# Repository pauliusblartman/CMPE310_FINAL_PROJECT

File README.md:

# CMPE310_FINAL_PROJECT
Final project for CMPE310.

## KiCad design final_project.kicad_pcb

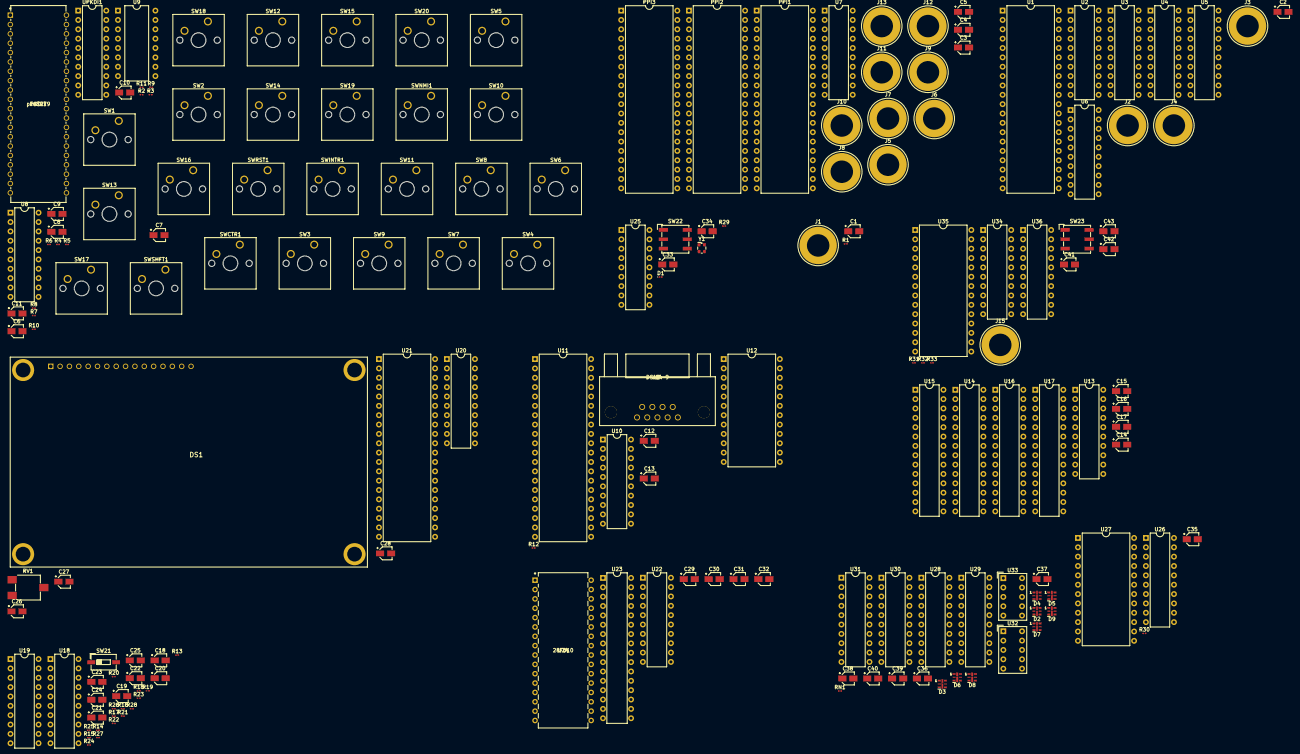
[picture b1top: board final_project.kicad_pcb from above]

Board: 2 copper layers, 173 parts (0 on the bottom side), 213 nets, no tracks yet.

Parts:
C1: 100uF; CP_Elec_3x5.3
C2, C3, C4, C5, C9, C12, C13, C14, C15, C16, C17, C26, C27, C34, C36, C37, C38, C39, C40, C41, C42, C43: 0.1uF; CP_Elec_3x5.3
C6, C7, C8, C10, C11: C; CP_Elec_3x5.3
C18, C19, C20, C21, C22, C23, C24, C25: C_Small; CP_Elec_3x5.3
C28, C29, C30, C31, C32, C35: .0000001; CP_Elec_3x5.3
C33: 10uF; CP_Elec_3x5.3
D1: DIODE; D_0201_0603Metric
D2, D3, D4, D5, D6, D7, D8, D9: LED; LED-APA102-2020
DS1: LCD4x20
J1: Conn_01x02_Female; Banana_Jack_1Pin
J2: Conn_01x20; Banana_Jack_1Pin
J3: Conn_01x16; Banana_Jack_1Pin
J4: Conn_01x10; Banana_Jack_1Pin
J5, J6, J7, J8, J9, J10, J11, J12, J13: Conn_01x08; Banana_Jack_1Pin
J14: DSUB-9
J15: Interrupt Header; Banana_Jack_1Pin
PKDI1: pkd8279
PPI1, PPI2, PPI3: 8255; DIP-40_W15.24mm
R1, R2, R3, R4, R5, R6, R7, R8, R9, R10, R11, R12, R13, R14, R15, R16, R17, R18, R19, R20, R21, R22, R23, R24, R25, R26, R27, R28, R32: R; R_0201_0603Metric
R29, R33: 10k; R_0201_0603Metric
R30, R31: 10000; R_0201_0603Metric
RN1: R_Network08; R_0201_0603Metric
RV1: 10000-20000; Potentiometer_ACP_CA6-VSMD_Vertical
SW1, SW2, SW3, SW4, SW5, SW6, SW7, SW8, SW9, SW10, SW11, SW12, SW13, SW14, SW15, SW16, SW17, SW18, SW19, SW20: SW_Push; SW_Cherry_MX_1.00u_PCB
SW21: SW_DIP_x08; SW_DIP_SPSTx01_Slide_6.7x4.1mm_W6.73mm_P2.54mm_LowProfile_J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
SW22, SW23: SW_Push; Nidec_Copal_SH-7010A
SWCTR1: SW_Push; SW_Cherry_MX_1.00u_PCB
SWINTR1: SW_Push; SW_Cherry_MX_1.00u_PCB
SWNMI1: SW_Push; SW_Cherry_MX_1.00u_PCB
SWRST1: SW_Push; SW_Cherry_MX_1.00u_PCB
SWSHFT1: SW_Push; SW_Cherry_MX_1.00u_PCB
U1: 8086_Min_Mode; DIP-40_W15.24mm
U2, U3: 74LS245; DIP-20_W7.62mm
U4, U5, U6: 74LS373; DIP-20_W7.62mm
U7, U10, U13, U19, U20, U22, U26, U28, U34: PAL16L8; DIP-20_W7.62mm
U8: 74LS540; DIP-20_W7.62mm
U9: 74HC237; DIP-16_W10.16mm
U11: 16550; DIP-40_W15.24mm
U12: max235cpg; DIP-24_W15.24mm
U14, U15, U16, U17: CY7C199; DIP-28_W7.62mm
U18, U36: 74LS244; DIP-20_W7.62mm
U21: 82C55A; DIP-40_W15.24mm
U23: 28F010; DIP-32_W7.62mm
U24: 28F010
U25: 8284; DIP-18_W7.62mm
U27: 8254; DIP-24_W15.24mm
U29, U30, U31: 74LS374; DIP-20_W7.62mm
U32, U33: HDSP-A151
U35: 8259; DIP-28_W15.24mm
UPKDI1: PAL16L8; DIP-20_W7.62mm
Y1: 15MHz; Oscillator_SMD_ECS_2520MV-xxx-xx-4Pin_2.5x2.0mm

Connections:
+3V3: R1.2, U9.4, U9.6
+5V: C1.1, C2.1, C3.1, C4.1, C5.1, C9.2, C12.2, C13.1, C14.1, C15.1, C16.1, C17.1, C26.1, C27.1, C28.2, C31.1, C32.1, C34.1, C35.1, C36.1, C37.1, C38.1, C39.1, C40.1, C41.1, C42.1, C43.2, D1.2, DS1.2, J1.1, PKDI1.40, PPI1.26, PPI2.26, PPI3.26, R1.1, R2.1, R4.1, R6.1, R8.1, R10.1, R12.2, R13.2, R14.2, R15.2, R16.2, R17.2, R18.2, R19.2, R20.2, R29.1, R30.1, R31.2, R33.1, RN1.1, RV1.3, SW23.2, U1.33, U1.40, U2.20, U3.20, U4.20, U5.20, U6.20, U7.20, U8.20, U9.16, U10.20, U11.40, U12.12, U13.20, U14.28, U15.28, U16.28, U17.28, U18.20, U19.20, U20.20, U21.26, U22.20, U23.17, U23.18, U23.19, U23.20, U23.21, U23.23, U23.25, U23.26, U23.27, U23.28, U23.29, U23.32, U24.17, U24.18, U24.19, U24.20, U24.21, U24.23, U24.25, U24.26, U24.27, U24.28, U24.29, U24.32, U25.18, U27.24, U28.20, U29.20, U30.20, U31.20, U32.1, U32.6, U33.1, U33.6, U34.20, U35.28, U36.20, UPKDI1.20
+12V: C29.2, C30.2, U23.1, U24.1
/8086/A0: J2.1, U4.2, U7.13, U10.1, U13.1, U19.11, U20.1, U26.1, UPKDI1.1
/8086/A1: PKDI1.21, PPI1.9, PPI2.9, PPI3.9, U4.5, U11.28, U14.21, U15.21, U16.21, U17.21, U19.9, U21.9, U27.19
/8086/A2: PPI1.8, PPI2.8, PPI3.8, U4.6, U11.27, U14.23, U15.23, U16.23, U17.23, U19.8, U21.8, U27.20, UPKDI1.2
/8086/A3: U4.9, U7.12, U11.26, U14.24, U15.24, U16.24, U17.24, U19.7, U20.2, U26.2, UPKDI1.3
/8086/A4: U4.12, U7.1, U10.2, U14.25, U15.25, U16.25, U17.25, U19.6, U20.3, U26.3, UPKDI1.4
/8086/A5: U4.15, U7.2, U10.3, U14.26, U15.26, U16.26, U17.26, U19.5, U20.4, U26.4, UPKDI1.5
/8086/A6: U4.16, U7.3, U10.4, U14.1, U15.1, U16.1, U17.1, U19.4, U20.5, U26.5, UPKDI1.6
/8086/A7: U4.19, U7.4, U10.5, U14.2, U15.2, U16.2, U17.2, U19.3, U20.6, U26.6, UPKDI1.7
/8086/A8: U6.2, U7.5, U10.6, U14.3, U15.3, U16.3, U17.3, U19.2, U20.7, U26.7, UPKDI1.8
/8086/A9: U6.5, U7.6, U10.7, U14.4, U15.4, U16.4, U17.4, U19.1, U20.8, U26.8, UPKDI1.9
/8086/A10: U6.6, U7.7, U10.8, U14.5, U15.5, U16.5, U17.5, U19.14, U20.9, U26.9, UPKDI1.11
/8086/A11: U6.9, U7.8, U10.9, U14.6, U15.6, U16.6, U17.6, U19.15, U20.11, U26.11
/8086/A12: U6.12, U7.9, U10.19, U14.7, U15.7, U16.7, U17.7, U19.16, U20.12, UPKDI1.15
/8086/A13: U6.15, U7.11, U10.18, U14.8, U15.8, U16.8, U17.8, U19.17, U20.13, U26.12, UPKDI1.14
/8086/A14: U6.16, U7.14, U10.17, U14.9, U15.9, U16.9, U17.9, U19.18, U20.14, U26.13, UPKDI1.13
/8086/A15: U6.19, U7.15, U10.16, U14.10, U15.10, U16.10, U17.10, U19.19, U20.15, U26.14, UPKDI1.12
/8086/A16: U5.2, U13.2
/8086/A17: U5.5, U13.3
/8086/A18: U5.6, U13.4
/8086/A19: U5.9, U13.5
/8086/AD0: U1.16, U2.2, U4.3
/8086/AD1: U1.15, U2.3, U4.4
/8086/AD2: U1.14, U2.4, U4.7
/8086/AD3: U1.13, U2.5, U4.8
/8086/AD4: U1.12, U2.6, U4.13
/8086/AD5: U1.11, U2.7, U4.14
/8086/AD6: U1.10, U2.8, U4.17
/8086/AD7: U1.9, U2.9, U4.18
/8086/AD8: U1.8, U3.2, U6.3
/8086/AD9: U1.7, U3.3, U6.4
/8086/AD10: U1.6, U3.4, U6.7
/8086/AD11: U1.5, U3.5, U6.8
/8086/AD12: U1.4, U3.6, U6.13
/8086/AD13: U1.3, U3.7, U6.14
/8086/AD14: U1.2, U3.8, U6.17
/8086/AD15: U1.39, U3.9, U6.18
/8086/BHE': J4.1, U1.34, U13.6, U22.3
/8086/CLK: U1.19, U25.8, U27.9, U27.15, U27.18
/8086/D0: DS1.7, J3.1, PKDI1.12, PPI2.34, U2.18, U15.11, U17.11, U18.18, U21.4, U21.34
/8086/D1: DS1.8, PKDI1.13, PPI2.33, U2.17, U15.12, U17.12, U18.16, U21.3, U21.33
/8086/D2: DS1.9, PKDI1.14, PPI2.32, U2.16, U15.13, U17.13, U18.14, U21.2, U21.32
/8086/D3: DS1.10, PKDI1.15, PPI2.31, U2.15, U15.15, U17.15, U18.12, U21.1, U21.31
/8086/D4: DS1.11, PKDI1.16, PPI2.30, U2.14, U15.16, U17.16, U18.9, U21.30, U21.40
/8086/D5: DS1.12, PKDI1.17, PPI2.29, U2.13, U15.17, U17.17, U18.7, U21.29, U21.39
/8086/D6: DS1.13, PKDI1.18, PPI2.28, U2.12, U15.18, U17.18, U18.5, U21.28, U21.38
/8086/D7: DS1.14, PKDI1.19, PPI2.27, U2.11, U15.19, U17.19, U18.3, U21.27, U21.37
/8086/D8: PPI1.34, PPI3.34, U3.18, U11.1, U14.11, U16.11
/8086/D9: PPI1.33, PPI3.33, U3.17, U11.2, U14.12, U16.12
/8086/D10: PPI1.32, PPI3.32, U3.16, U11.3, U14.13, U16.13
/8086/D11: PPI1.31, PPI3.31, U3.15, U11.4, U14.15, U16.15
/8086/D12: PPI1.30, PPI3.30, U3.14, U11.5, U14.16, U16.16
/8086/D13: PPI1.29, PPI3.29, U3.13, U11.6, U14.17, U16.17
/8086/D14: PPI1.28, PPI3.28, U3.12, U11.7, U14.18, U16.18
/8086/D15: PPI1.27, PPI3.27, U3.11, U11.8, U14.19, U16.19
/8086/INTA': U1.24, U35.26
/8086/INTR: U1.18, U8.12, U11.30, U35.17, U35.21
/8086/M-IO': U1.28, U7.16, U10.11, U13.7, U19.13, U22.4, U34.1, UPKDI1.16
/8086/NMI: U1.17, U8.13
/8086/Ready: U1.22, U25.5
/8254/CS': U26.19, U27.21
/8254/IR1: U27.13, U35.19
/8259/IR2: PKDI1.4, U35.20
/8259/SW: R32.2, U35.18
/8279 and Keys/CLK: PKDI1.3, U11.16, U25.2, U29.11, U30.11
/8284A/RESET: PKDI1.9, PPI1.35, PPI2.35, PPI3.35, U1.21, U8.11, U11.35, U21.35, U25.10
/CMOS/A[1]: U23.12, U24.12
/CMOS/A[2]: U23.11, U24.11
/CMOS/A[3]: U23.10, U24.10
/CMOS/A[4]: U23.9, U24.9
/CMOS/A[5]: U23.8, U24.8
/CMOS/A[6]: U23.7, U24.7
/CMOS/A[7]: U23.6, U24.6
/CMOS/A[8]: U23.5, U24.5
/CMOS/A[13]: U23.4, U24.4
/CMOS/A[16]: U23.3, U24.3
/CMOS/A[17]: U23.2, U24.2
/CMOS/OE': PKDI1.10, PPI1.5, PPI2.5, PPI3.5, U1.32, U11.21, U14.22, U15.22, U16.22, U17.22, U21.5, U23.24, U24.24, U27.22, U35.3
/CMOS/WE': PKDI1.11, PPI1.36, PPI2.36, PPI3.36, U1.29, U11.18, U14.27, U15.27, U16.27, U17.27, U21.36, U23.31, U24.31, U27.23, U35.2
/LCD/E: DS1.6, U21.20
/LCD/RS: DS1.4, U21.19
/LCD/R\W': DS1.5, U21.18
/LED/0: U29.2, U30.2, U32.10, U33.10
/LED/1: U29.5, U30.5, U32.9, U33.9
/LED/2: U29.6, U30.6, U32.8, U33.8
/LED/3: U29.9, U30.9, U32.5, U33.5
/LED/4: U29.12, U30.12, U32.4, U33.4
/LED/5: U29.15, U30.15, U32.2, U33.2
/LED/6: U29.16, U30.16, U32.3, U33.3
/LED/7: U29.19, U30.19, U32.7, U33.7
/LED/D[0]: U29.3, U30.3, U31.3
/LED/D[1]: U29.4, U30.4, U31.4
/LED/D[2]: U29.7, U30.7, U31.7
/LED/D[3]: U29.8, U30.8, U31.8
/LED/D[4]: U29.13, U30.13, U31.13
/LED/D[5]: U29.14, U30.14, U31.14
/LED/D[6]: U29.17, U30.17, U31.17
/LED/D[7]: U29.18, U30.18, U31.18
GND: C1.2, C2.2, C3.2, C4.2, C5.2, C6.2, C7.2, C8.2, C9.1, C10.2, C11.2, C12.1, C13.2, C14.2, C15.2, C16.2, C17.2, C18.2, C19.2, C20.2, C21.2, C22.2, C23.2, C24.2, C25.2, C26.2, C27.2, C28.1, C29.1, C30.1, C31.2, C32.2, C33.2, C34.2, C35.2, C36.2, C37.2, C38.2, C39.2, C40.2, C41.2, C42.2, C43.1, DS1.1, DS1.15, DS1.16, J14.5, PKDI1.20, PPI1.7, PPI2.7, PPI3.7, RV1.1, SW21.1, SW21.2, SW22.1, SWCTR1.2, SWINTR1.2, SWNMI1.2, SWRST1.2, SWSHFT1.2, U1.1, U1.20, U2.10, U3.10, U4.1, U4.10, U5.1, U5.10, U6.1, U6.10, U7.10, U8.1, U8.10, U8.19, U9.5, U9.8, U10.10, U11.19, U11.20, U11.22, U11.25, U12.11, U12.20, U12.21, U13.10, U14.14, U15.14, U16.14, U17.14, U18.10, U19.10, U20.10, U21.7, U22.10, U23.16, U24.16, U25.1, U25.3, U25.4, U25.6, U25.7, U25.9, U25.13, U27.12, U28.10, U29.10, U30.10, U31.1, U31.10, U34.10, U35.14, U36.1, U36.10, U36.19, UPKDI1.10
unnamed: C6.1, R3.1, U8.9
unnamed: C7.1, R5.1, U8.8
unnamed: C8.1, R7.1, U8.7
unnamed: C10.1, R9.1, U8.6
unnamed: C11.1, R11.1, U8.5
unnamed: C18.1, R21.1, U18.2
unnamed: C19.1, R22.1, U18.4
unnamed: C20.1, R23.1, U18.6
unnamed: C21.1, R24.1, U18.8
unnamed: C22.1, R25.1, U18.11
unnamed: C23.1, R26.1, U18.13
unnamed: C24.1, R27.1, U18.15
unnamed: C25.1, R28.1, U18.17
unnamed: C33.1, D1.1, R29.2, SW22.2, U25.11
unnamed: D2.1, U31.19
unnamed: D3.1, U31.16
unnamed: D4.1, U31.15
unnamed: D5.1, U31.12
unnamed: D6.1, U31.9
unnamed: D7.1, U31.6
unnamed: D8.1, U31.5
unnamed: D9.1, U31.2
unnamed: D9.2, RN1.2
unnamed: DS1.3, RV1.2
unnamed: J5.1, PPI1.4
unnamed: J6.1, PPI1.18
unnamed: J7.1, PPI1.14
unnamed: J8.1, PPI2.4
unnamed: J9.1, PPI2.18
unnamed: J10.1, PPI2.14
unnamed: J11.1, PPI3.4
unnamed: J12.1, PPI3.14
unnamed: J13.1, PPI3.18
unnamed: J14.1, U12.5
unnamed: J14.2, U12.10
unnamed: J14.3, U12.2
unnamed: J14.4, U12.4
unnamed: J14.6, U12.13
unnamed: J14.7, U12.3
unnamed: J14.8, U12.18
unnamed: J14.9, U12.24
unnamed: J15.1, U36.2
unnamed: PKDI1.1, SW3.1, SW7.1, SW11.1, SW15.1, SW19.1
unnamed: PKDI1.2, SW4.1, SW8.1, SW12.1, SW16.1, SW20.1
unnamed: PKDI1.22, UPKDI1.19
unnamed: PKDI1.32, U9.1
unnamed: PKDI1.33, U9.2
unnamed: PKDI1.34, U9.3
unnamed: PKDI1.36, U8.15
unnamed: PKDI1.37, U8.14
unnamed: PKDI1.38, SW1.1, SW5.1, SW9.1, SW13.1, SW17.1
unnamed: PKDI1.39, SW2.1, SW6.1, SW10.1, SW14.1, SW18.1
unnamed: PPI1.6, U7.17
unnamed: PPI2.6, U7.18
unnamed: PPI3.6, U7.19
unnamed: R2.2, R3.2, SWRST1.1
unnamed: R4.2, R5.2, SWINTR1.1
unnamed: R6.2, R7.2, SWNMI1.1
unnamed: R8.2, R9.2, SWCTR1.1
unnamed: R10.2, R11.2, SWSHFT1.1
unnamed: R12.1, U11.12, U11.13
unnamed: R13.1, R21.2
unnamed: R14.1, R22.2
unnamed: R15.1, R23.2
unnamed: R16.1, R24.2
unnamed: R17.1, R25.2
unnamed: R18.1, R26.2
unnamed: R19.1, R27.2
unnamed: R20.1, R28.2
unnamed: R30.2, U27.11, U27.14, U27.16
unnamed: R31.1, U35.16
unnamed: R32.1, R33.2, SW23.1
unnamed: SW1.2, SW2.2, SW3.2, SW4.2, U9.11
unnamed: SW5.2, SW6.2, SW7.2, SW8.2, U9.12
unnamed: SW9.2, SW10.2, SW11.2, SW12.2, U9.13
unnamed: SW13.2, SW14.2, SW15.2, SW16.2, U9.14
unnamed: SW17.2, SW18.2, SW19.2, SW20.2, U9.15
unnamed: U1.25, U4.11, U5.11, U6.11
unnamed: U1.26, U2.19, U3.19
unnamed: U1.27, U2.1, U3.1
unnamed: U1.35, U5.8
unnamed: U1.36, U5.7
unnamed: U1.37, U5.4
unnamed: U1.38, U5.3
unnamed: U10.12, U11.14
unnamed: U11.10, U12.9
unnamed: U11.11, U12.15
unnamed: U11.9, U11.15
unnamed: U11.32, U12.8
unnamed: U11.33, U12.7
unnamed: U11.36, U12.17
unnamed: U11.37, U12.14
unnamed: U11.38, U12.6
unnamed: U11.39, U12.23
unnamed: U13.16, U15.20
unnamed: U13.17, U17.20
unnamed: U13.18, U16.20
unnamed: U13.19, U14.20
unnamed: U18.1, U18.19, U19.12
unnamed: U20.19, U21.6
unnamed: U22.18, U24.22
unnamed: U22.19, U23.22
unnamed: U25.16, Y1.2
unnamed: U25.17, Y1.1
unnamed: U28.17, U31.11
unnamed: U28.18, U30.1
unnamed: U28.19, U29.1
unnamed: U34.18, U35.1
unnamed: U35.22, U36.18
unnamed: U35.23, U36.16
unnamed: U35.24, U36.14
unnamed: U35.25, U36.12

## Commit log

2021-12-12 8086,SRAM,8255,8279 complete
2021-12-12 UART
2021-12-13 Merged 8254
2021-12-13 LCD Up
2021-12-13 Integrated LCD. Fixed issues with busses
2021-12-14 All schematics present
2021-12-14 Wired Root
2021-12-14 Added external headers
2021-12-14 Fixing Weirdness
2021-12-14 Started PCB
2021-12-14 Readd LCD changes.
2021-12-14 CMOS power fix
2021-12-14 Bleh
2021-12-14 LCD fixed
2021-12-14 Missed some labels

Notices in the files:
parts and their libraries:
Copyright 2016 Accelerated Designs. All rights reserved.
